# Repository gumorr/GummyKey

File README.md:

# GummyKey
a split keyboard that i made

## How to build

im too lazy to write a comprehensive build guide, so just know a lot of the steps in building a solfe keyboard will apply to this

## BOM

|Component|Location|QTY|
|---------|--------|---|
|Pro Micro|U1|2|
|[TRRS Jack](https://www.aliexpress.us/item/2255800474897706.html)|J1|2|
|[2 Pin Tactile Button](https://www.aliexpress.us/item/3256802304413347.html)|SW1|2|
|[4.7K Resistor, 0805](https://www.mouser.com/ProductDetail/603-RC0805FR-104K7L)|R1,R2|4|
|[1N4148W Diode, SOD123](https://mou.sr/3kOR7fV)|D1-29|58|
|[Kailh Cherry Hot-Swap Socket](https://www.aliexpress.us/item/2255800865526224.html)|K1-29|58|

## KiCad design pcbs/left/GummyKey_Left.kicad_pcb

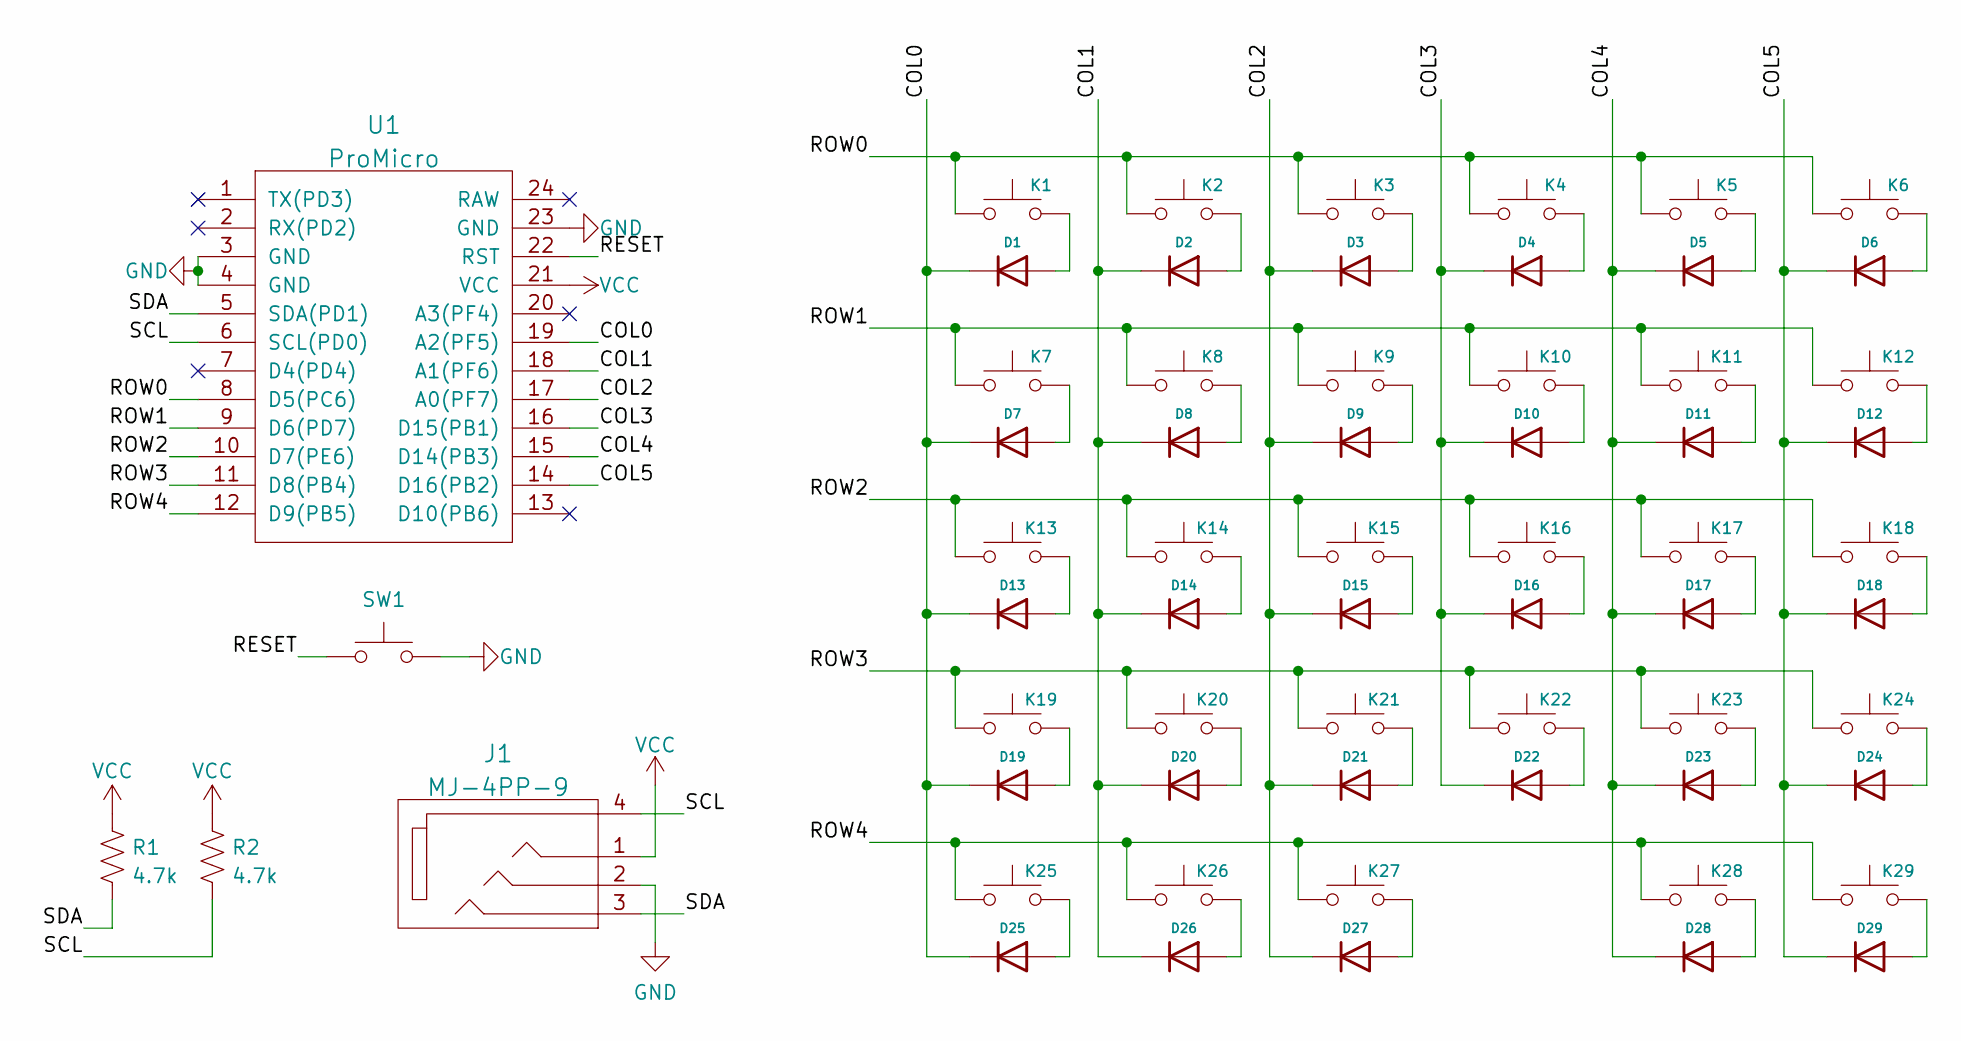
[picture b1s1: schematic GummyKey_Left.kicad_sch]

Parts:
D1, D2, D3, D4, D5, D6, D7, D8, D9, D10, D11, D12, D13, D14, D15, D16, D17, D18, D19, D20, D21, D22, D23, D24, D25, D26, D27, D28, D29: D; D_SOD-123
J1: MJ-4PP-9
K1, K2, K3, K4, K5, K6, K7, K8, K9, K10, K11, K12, K13, K14, K15, K16, K17, K18, K19, K20, K21, K22, K23, K24, K25, K26, K27, K28, K29: SW_Push; SW_Hotswap_Kailh_MX_1.00u
R1, R2: 4.7k; R_0805_2012Metric_Pad1.20x1.40mm_HandSolder
SW1: SW_Push; Reset_Switch
U1: ProMicro

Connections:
/COL0: D1.1 (K), D7.1 (K), D13.1 (K), D19.1 (K), D25.1 (K), U1.19 (A2(PF5))
/COL1: D2.1 (K), D8.1 (K), D14.1 (K), D20.1 (K), D26.1 (K), U1.18 (A1(PF6))
/COL2: D3.1 (K), D9.1 (K), D15.1 (K), D21.1 (K), D27.1 (K), U1.17 (A0(PF7))
/COL3: D4.1 (K), D10.1 (K), D16.1 (K), D22.1 (K), U1.16 (D15(PB1))
/COL4: D5.1 (K), D11.1 (K), D17.1 (K), D23.1 (K), D28.1 (K), U1.15 (D14(PB3))
/COL5: D6.1 (K), D12.1 (K), D18.1 (K), D24.1 (K), D29.1 (K), U1.14 (D16(PB2))
/RESET: SW1.1, U1.22 (RST)
/ROW0: K1.1, K2.1, K3.1, K4.1, K5.1, K6.1, U1.8 (D5(PC6))
/ROW1: K7.1, K8.1, K9.1, K10.1, K11.1, K12.1, U1.9 (D6(PD7))
/ROW2: K13.1, K14.1, K15.1, K16.1, K17.1, K18.1, U1.10 (D7(PE6))
/ROW3: K19.1, K20.1, K21.1, K22.1, K23.1, K24.1, U1.11 (D8(PB4))
/ROW4: K25.1, K26.1, K27.1, K28.1, K29.1, U1.12 (D9(PB5))
/SCL: J1.4, R2.2, U1.6 (SCL(PD0))
/SDA: J1.3, R1.2, U1.5 (SDA(PD1))
GND: J1.2, SW1.2, U1.3 (GND), U1.4 (GND), U1.23 (GND)
unnamed: D1.2 (A), K1.2
unnamed: D2.2 (A), K2.2
unnamed: D3.2 (A), K3.2
unnamed: D4.2 (A), K4.2
unnamed: D5.2 (A), K5.2
unnamed: D6.2 (A), K6.2
unnamed: D7.2 (A), K7.2
unnamed: D8.2 (A), K8.2
unnamed: D9.2 (A), K9.2
unnamed: D10.2 (A), K10.2
unnamed: D11.2 (A), K11.2
unnamed: D12.2 (A), K12.2
unnamed: D13.2 (A), K13.2
unnamed: D14.2 (A), K14.2
unnamed: D15.2 (A), K15.2
unnamed: D16.2 (A), K16.2
unnamed: D17.2 (A), K17.2
unnamed: D18.2 (A), K18.2
unnamed: D19.2 (A), K19.2
unnamed: D20.2 (A), K20.2
unnamed: D21.2 (A), K21.2
unnamed: D22.2 (A), K22.2
unnamed: D23.2 (A), K23.2
unnamed: D24.2 (A), K24.2
unnamed: D25.2 (A), K25.2
unnamed: D26.2 (A), K26.2
unnamed: D27.2 (A), K27.2
unnamed: D28.2 (A), K28.2
unnamed: D29.2 (A), K29.2
VCC: J1.1, R1.1, R2.1, U1.21 (VCC)

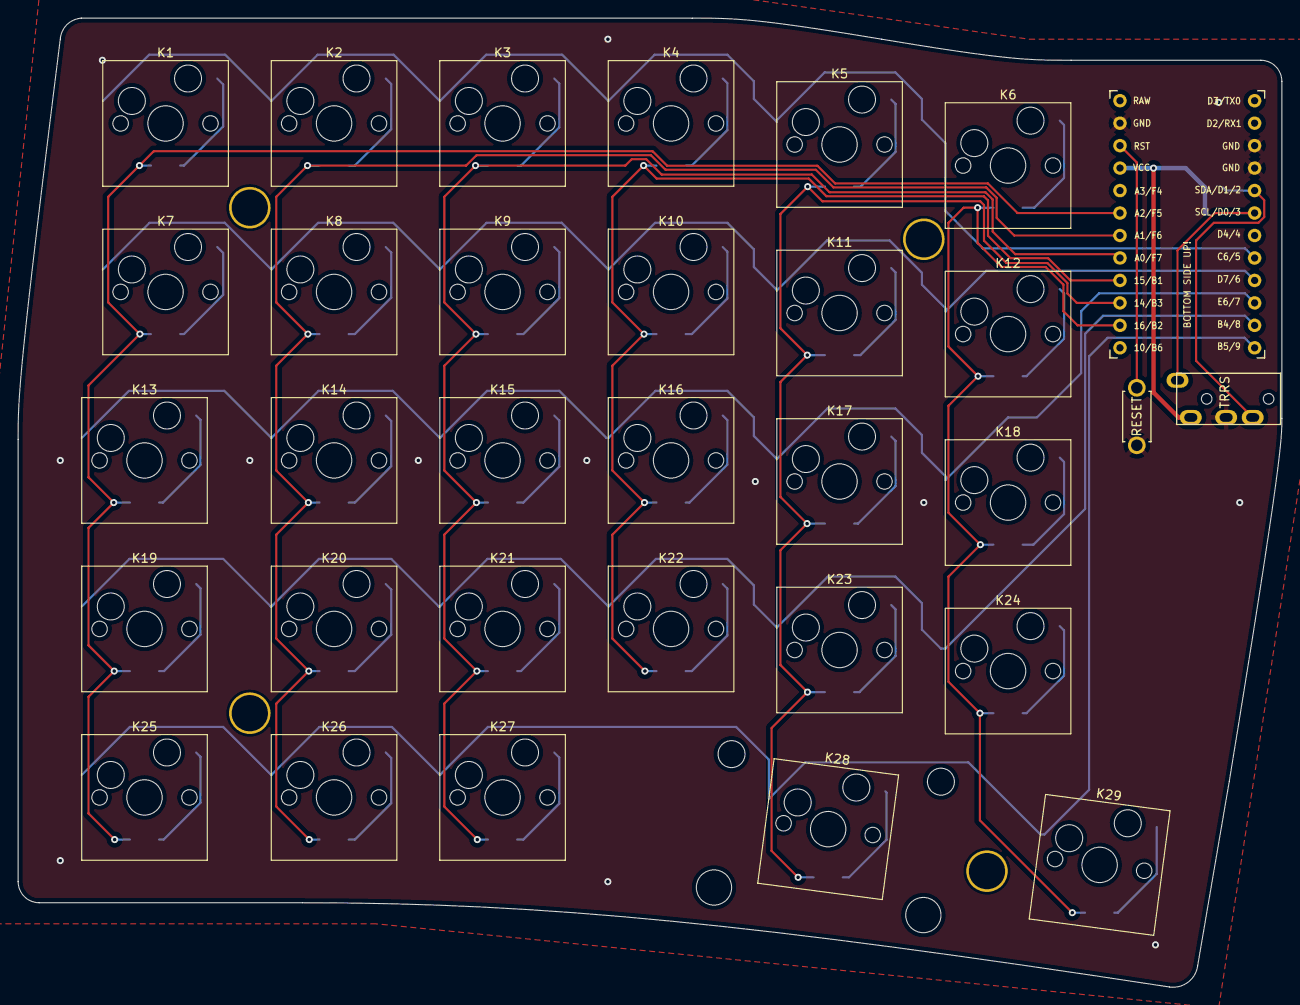
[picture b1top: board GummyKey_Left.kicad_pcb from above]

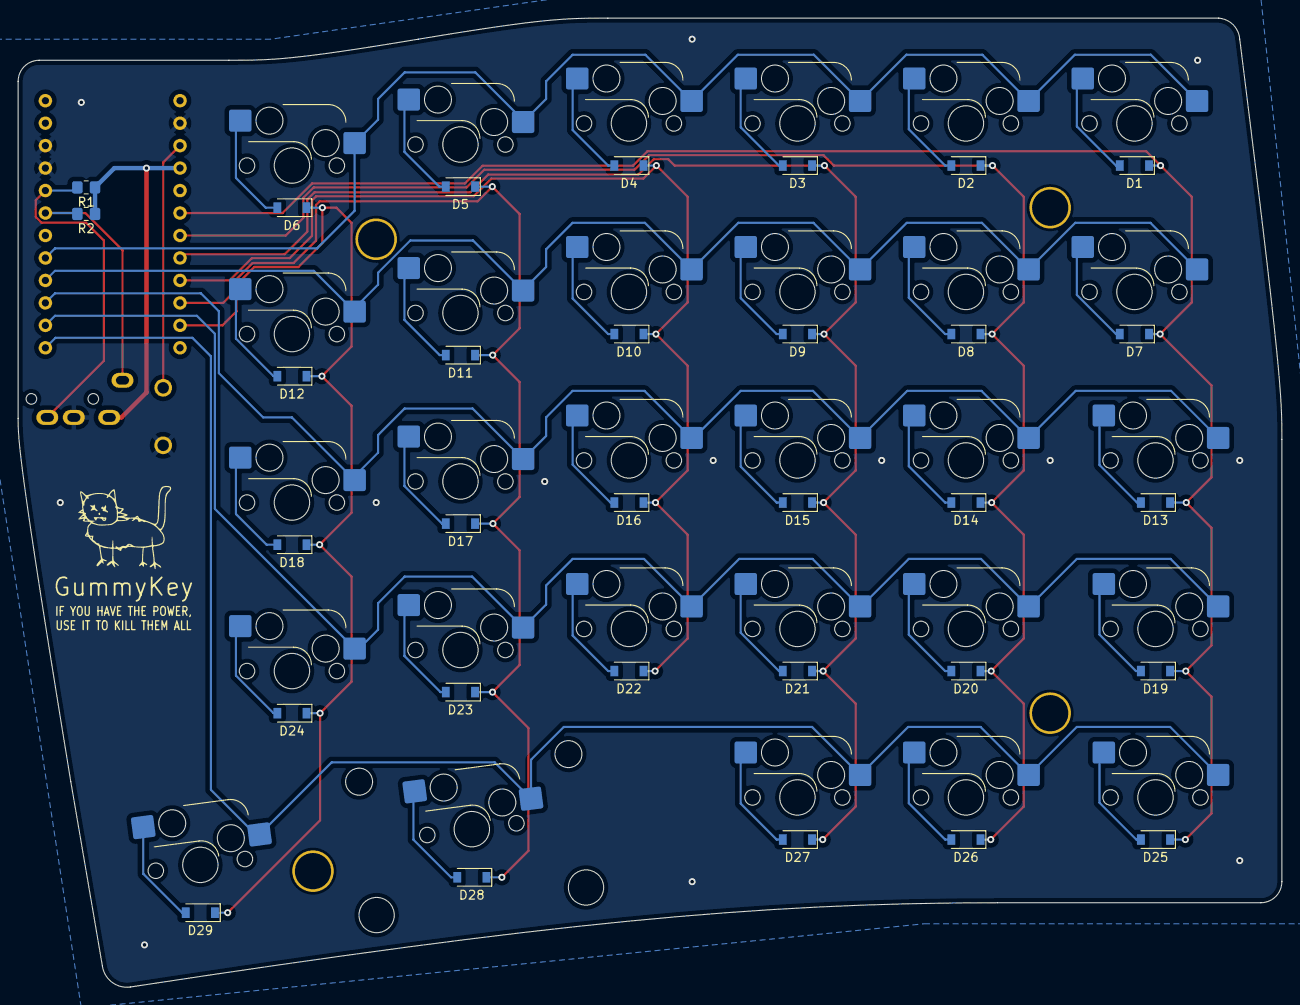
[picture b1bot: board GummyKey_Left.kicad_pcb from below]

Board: 2 copper layers, 142.9 x 109.6 mm, 67 parts (31 on the bottom side), 45 nets.

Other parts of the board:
TH3, TH3#2, TH3#3, TH3#4: HOLE; M2_Hole
